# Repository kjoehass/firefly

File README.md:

# firefly

The goal of this project is to develop a device that can simulate the flash patterns of fireflies. The device will be used to investigate evolution and speciation in fireflies.

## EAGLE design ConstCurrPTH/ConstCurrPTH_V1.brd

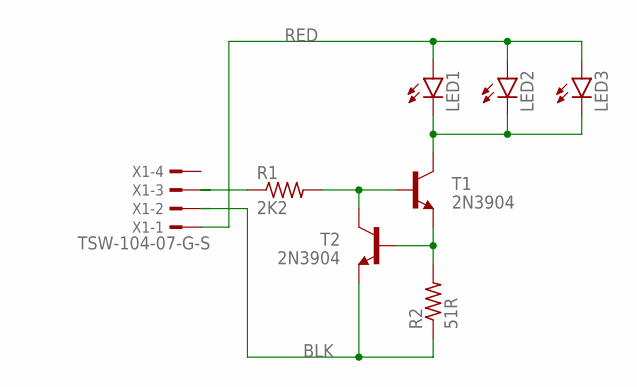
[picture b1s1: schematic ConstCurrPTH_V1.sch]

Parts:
LED1: LED3MM
LED2: LEDCHIPLED_0805; CHIPLED_0805
LED3: LEDCHIPLED_1206; CHIPLED_1206
R1: 2K2; 0207/10
R2: 51R; 0207/10
T1, T2: 2N3904; TO92
X1: TSW-104-07-G-S; TSW-104-XX-G-S

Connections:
BLK: R2.1, T2.3 (E), X1.2
unnamed: LED1.K (C), LED2.C, LED3.C, T1.1 (C)
unnamed: R2.2, T1.3 (E), T2.2 (B)
unnamed: R1.2, T1.2 (B), T2.1 (C)
unnamed: R1.1, X1.3
RED: LED1.A, LED2.A, LED3.A, X1.1

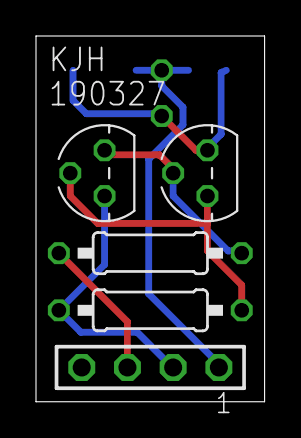
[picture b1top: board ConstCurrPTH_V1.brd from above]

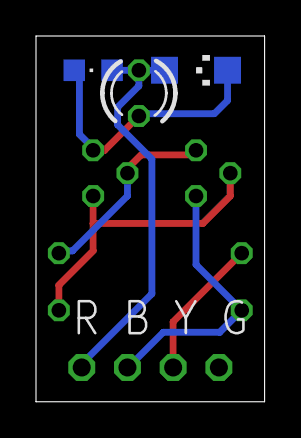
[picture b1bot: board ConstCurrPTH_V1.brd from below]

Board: 2 copper layers, 12.7 x 20.3 mm, 8 parts (3 on the bottom side), 6 nets.

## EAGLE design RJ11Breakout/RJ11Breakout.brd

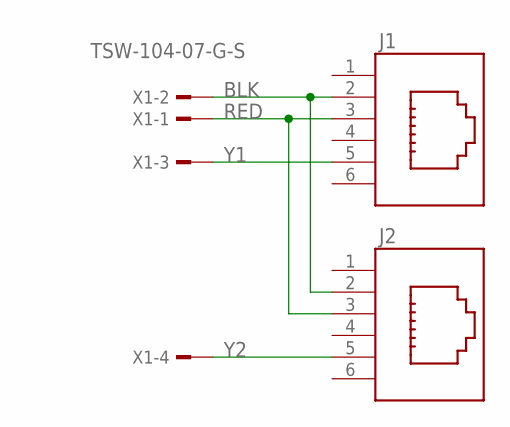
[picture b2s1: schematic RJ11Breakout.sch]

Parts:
J1, J2: 615006138421
X1: TSW-104-07-G-S; TSW-104-XX-G-S

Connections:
BLK: J1.2 (5), J2.2 (5), X1.2
RED: J1.3 (4), J2.3 (4), X1.1
Y1: J1.5 (2), X1.3
Y2: J2.5 (2), X1.4

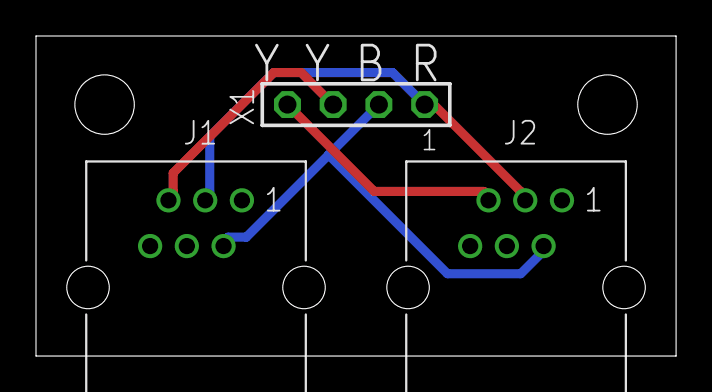
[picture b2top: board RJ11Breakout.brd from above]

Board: 2 copper layers, 35.6 x 17.8 mm, 3 parts (0 on the bottom side), 4 nets.

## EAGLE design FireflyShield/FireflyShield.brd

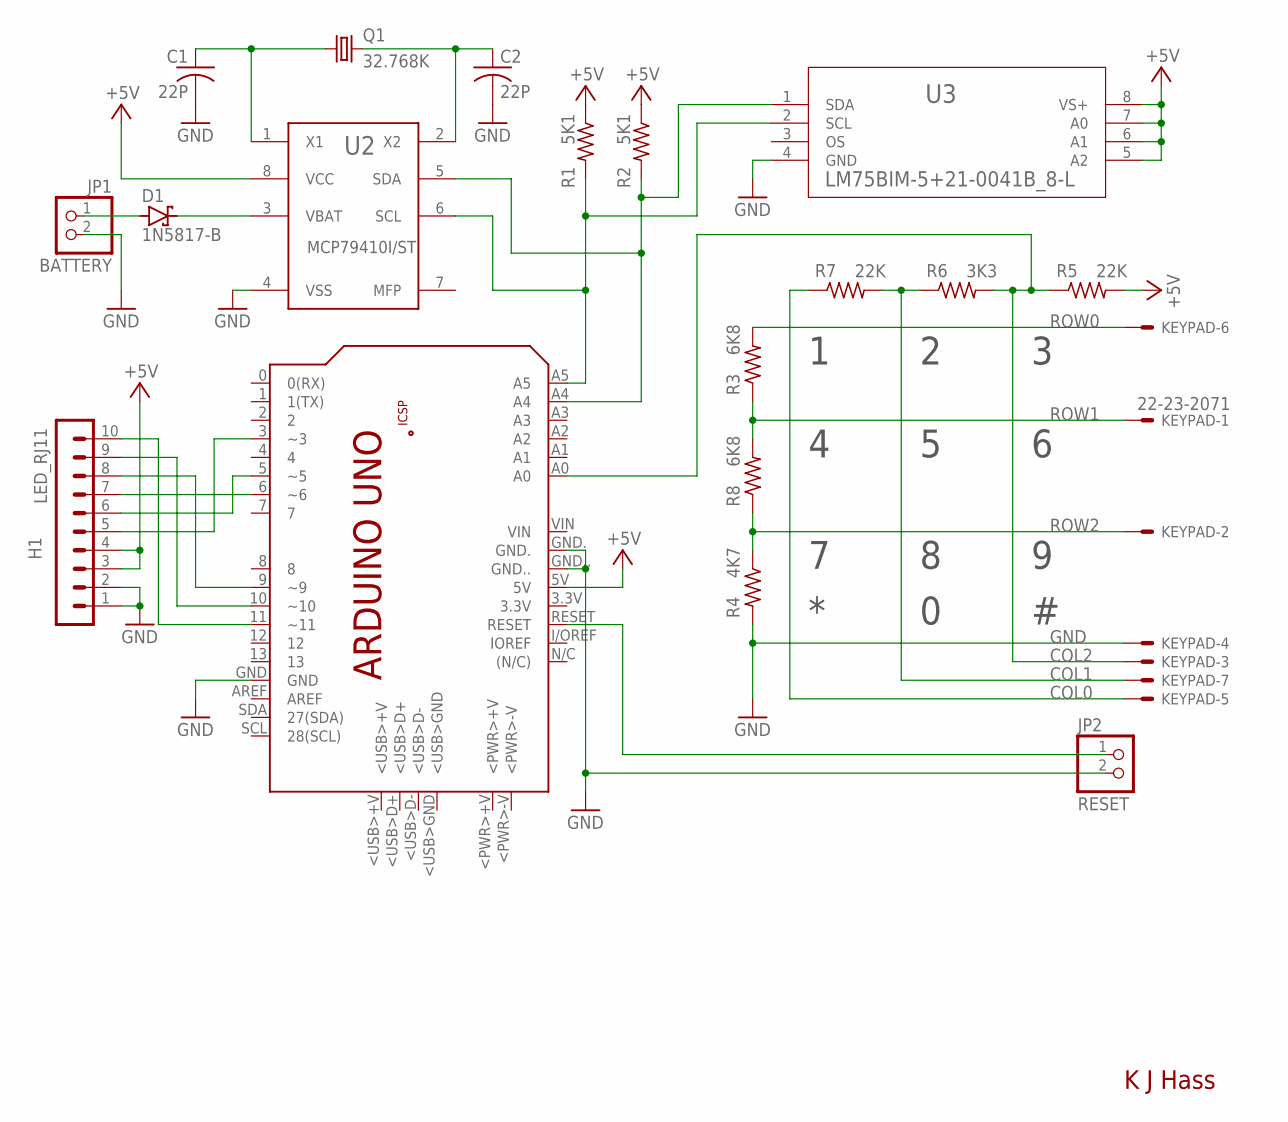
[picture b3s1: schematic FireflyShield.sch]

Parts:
C1, C2: 22P; C0805
D1: 1N5817-B; DO41-7.6
H1: LED_RJ11; MA10-1
JP1: BATTERY; 1X02
JP2: RESET; 1X02
KEYPAD: 22-23-2071
PCB1: ARDUINO_UNO
Q1: 32.768K; TC26V
R1, R2: 5K1; 0207/10
R3, R8: 6K8; 0207/10
R4: 4K7; 0207/10
R5, R7: 22K; 0207/10
R6: 3K3; 0207/10
U2: MCP79410I/ST; TSSOP8_4MM4
U3: LM75BIM-5+21-0041B_8-L; 21-0041B_8-L

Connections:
+5V: H1.3, H1.4, PCB1.5V, R1.1, R2.1, R5.2, U2.8 (VCC), U3.5 (A2), U3.6 (A1), U3.7 (A0), U3.8 (VS+)
COL0: KEYPAD.5, R7.1
COL1: KEYPAD.7, R6.1, R7.2
COL2: KEYPAD.3, PCB1.A0, R5.1, R6.2
GND: C1.2, C2.2, H1.1, H1.2, JP1.2, JP2.2, KEYPAD.4, PCB1.GND, PCB1.GND., PCB1.GND.., R4.2, U2.4 (VSS), U3.4 (GND)
unnamed: PCB1.A5, R1.2, U2.6 (SCL), U3.2 (SCL)
unnamed: H1.5, PCB1.3 (~3)
unnamed: H1.6, PCB1.5 (~5)
unnamed: H1.7, PCB1.6 (~6)
unnamed: H1.8, PCB1.9 (~9)
unnamed: H1.9, PCB1.10 (~10)
unnamed: H1.10, PCB1.11 (~11)
unnamed: JP2.1, PCB1.RESET
unnamed: C1.1, Q1.1, U2.1 (X1)
unnamed: C2.1, Q1.2, U2.2 (X2)
unnamed: D1.C, U2.3 (VBAT)
unnamed: D1.A, JP1.1
ROW0: KEYPAD.6, R3.2
ROW1: KEYPAD.1, R3.1, R8.2
ROW2: KEYPAD.2, R4.1, R8.1
SCL: PCB1.A4, R2.2, U2.5 (SDA), U3.1 (SDA)

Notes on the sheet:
K J Hass

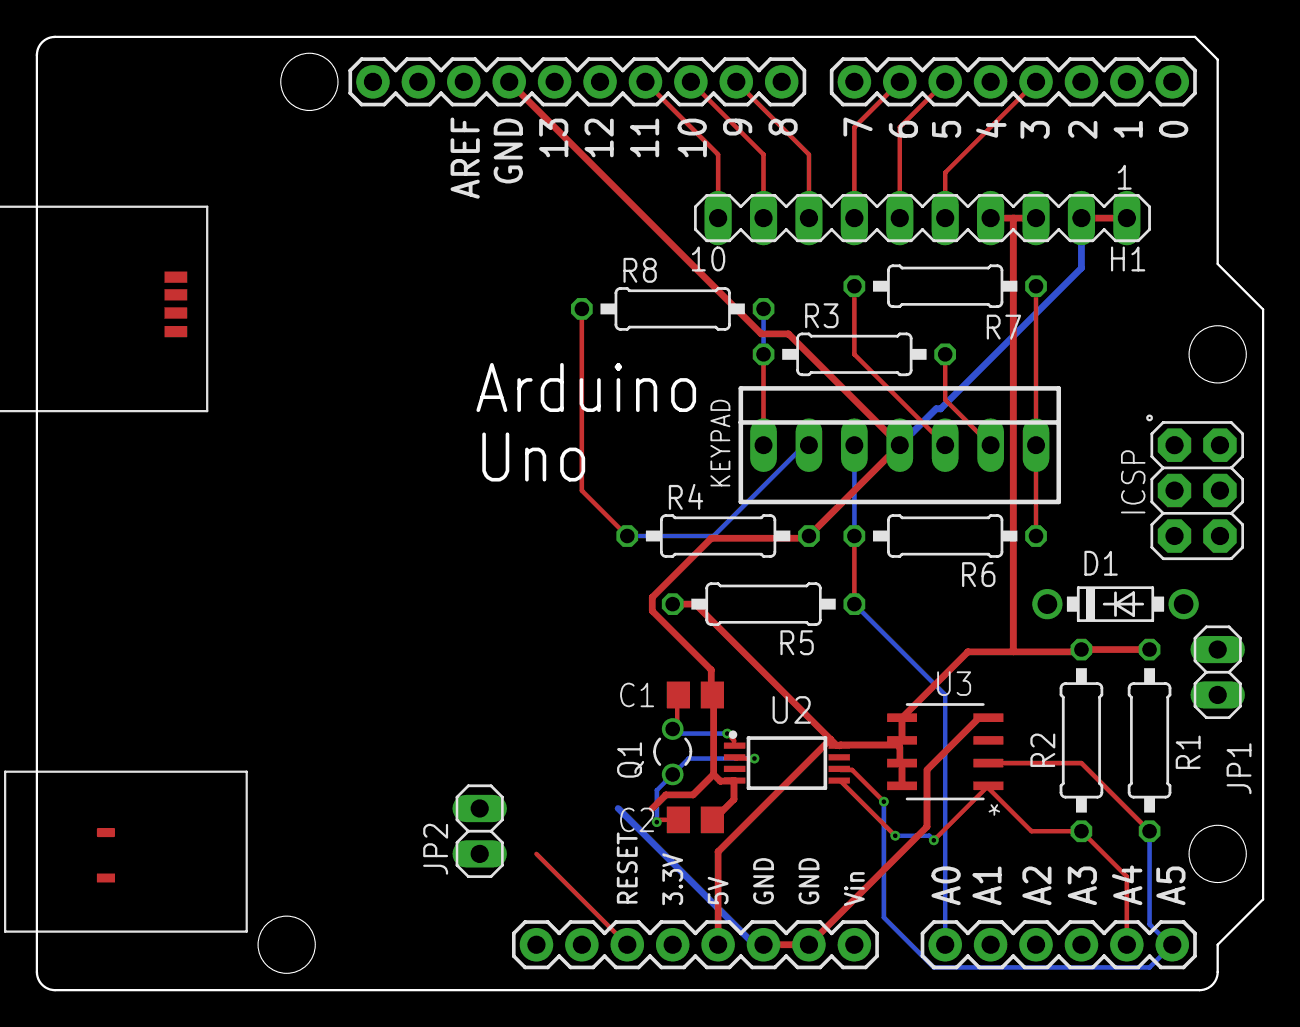
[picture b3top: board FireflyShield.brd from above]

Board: 2 copper layers, 68.6 x 53.3 mm, 19 parts (0 on the bottom side), 21 nets.

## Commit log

2019-03-18 Add README and LICENSE
2019-03-29 RealTimeClock and TempSensor have working code; they are not stubs
2019-03-31 test
2019-04-01 Completed Demo
2019-04-07 Added Temp and Clock Functionality
2019-04-11 Fixed Flash Pattern Interval
2019-04-11 Added Matt's code to main branch
2019-04-14 Created project-wide header file
2019-04-17 Added doxygen settings to the repo
2019-04-17 Added FAKE_RTC macro in case RTC is absent
2019-04-17 Added multiple inclusion guard to header file Slight changes in formatting
2019-04-17 Use ARDUINO_IS_UNO to set MaxChannel Change DisplayLED, DisplayFlash, DisplayPattern to just Display Store virtual channel number as LED::Channel, not pin number Display functions use HUMAN_READABLE_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
2019-04-17 Fixed typo in RealTimeClock comments
2019-04-23 Virtual LED Channel Correction
2019-04-24 Disabled FAKE_RTC...we have a working RTC now
2019-04-24 Added multiple inclusion guard
2019-04-24 First version of AnalogKeypad
2019-04-25 Updated specification to include dump messages, real-time clock, and keypad
2019-04-25 First version of shield schematic and PCB
2019-04-26 Better symbols/footprints for LM75, MCP79400
2019-04-30 Add RTC battery connection
2019-05-01 Added hardware design files
2019-05-01 Defined random pattern set & time config messages
2019-05-06 Added datasheets and OSHPark board images
2019-05-07 Clean up Random Pattern Set Config section
2019-05-07 Added Random Pattern Set class and methods
2019-05-07 Initialize TempC, removes warning
2019-05-19 Fix Pattern::Display, add Execute functions
2019-05-19 Fixed definition/declaration of objects, added keypad
2019-05-19 Added RandomPattern support, fixed declarations
2019-05-19 Modified Execute functions
2019-05-19 Rename Firefly.ino...stupid IDE
2019-05-23 Fixed Declarations
2019-05-23 Fixed Flash Exe Fuction
2019-05-23 Ensures up & down dur are multiples of 10
2019-05-23 First commit of user manual
2019-05-23 Stopped tracking .gitignore
2019-05-31 Accidental timestamp change
2019-05-31 First draft
2019-05-31 Added support for Capacity Response Message
2019-06-19 Fixed wire color order on LED board
2019-06-19 First commit of gui code
2019-06-20 Fixed pattern.dump() (missing IPI)
2019-07-03 Added configure() to configure simulator
2019-07-03 Added comments
2019-07-03 Added update_config() call when frame changes
2019-07-03 Added update_config(), fixed on_move()
2019-07-03 Fix handling of flash radio buttons
2019-07-03 Added FPI value to pattern lines
2019-07-03 Added on_tosim(), fixed on_tofile()
2019-07-22 Added LED configuration frame
2019-07-22 Restrict file selection dialogs to csv files
2019-07-22 Changed size of some arrays for clearer indexing
2019-07-22 Improved get_leds()
2019-07-22 Added frame to configure LEDs
2019-07-29 Changes kept or discarded. Spinboxes for patterns
    The code keeps track (crudely) of when an LED, flash, or pattern
    as been modified. The user is required to explicitly keep or
    discard any changes before beginning to edit a different LED, flash,
    or pattern.
    Spinboxes are used to select the flashes in a pattern, rather than
    two sets of radiobuttons.
2019-08-02 Improved detection of changed configuration
    Added a __eq__ method for all of the firefly data classes. Whenever
    the user clicks on a widget we check to see if the class instance
    actually changed from the stored configuration value. The user is
    only forced to save/discard changes if the instance is different
    from the stored version.
2019-08-06 Cleaned comments, added Execute frame
    Some comments, docstrings, and indenting were cleaned up after
    running pylint. The Execute frame was added to execute an LED,
    a flash, a pattern, or a pattern set. The Startpage functions
    were modified to explicitly close the serial connection. Startpage
    was also modified to handle the "Cancel" buttons of the file
    selection dialog boxes.
2019-08-19 Added config_Time() function
2019-08-19 Improved handling of FAKERTC code
2019-08-19 Fixed formatting for Arduino IDE
2019-08-19 Changed comment blocks to Arduino IDE style
2019-09-22 Cleanup and add comments
2019-09-22 Add serial print to Pattern::Execute, minor cleanups
2019-09-22 Do not define FAKE_RTC, use the real thing
2019-09-22 Add doxygen comments, remove disp_pattern function
    The functionality of the disp_pattern function was moved to
    Config_Data.cpp, the only place it was used.
2020-07-17 Added files for lasercutting the wood box
2020-07-31 No real change to project
2020-08-04 New box design, tabs are now 0.25 inch
2020-08-04 Improve flash timing, random patterns, keypad
    ExeMsg.cpp Calls LED.setLevel() to set illumination, does not set
    pinMode for PWM pins (moved to setup).
    Removed flash_led() (moved to fl.Execute())
    exec_flash() simplified, uses fl.Execute()
    exec_pattern() simplified, uses pt.Execute()
    Removed gen_rand_flash()...random pattern code was never
2021-01-25 Opened with new version of eagle?
2021-01-25 Add pdf version of schematic
2021-01-25 Add checks for valid definitions in csv file
2021-01-26 Detect if modifying flash duration breaks pattern
2021-01-26 Handle exception if can't open serial port
2021-01-26 Improved information messages for Arduino comms
2021-01-26 Fixed code that sets year in Arduino RTC
2021-01-26 First README for the Arduino code
2021-04-15 Fixed config of PWM pins in setup()
2021-04-15 Changed error message in exec_led()
2021-04-15 Fixed bug in config_LED()
    Bug would not allow channel 6 or LED 16 to be used.

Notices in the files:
parts and their libraries:
Wurth_Elektronik_Electromechanic_Input-O: Copyright: Würth Elektronik
